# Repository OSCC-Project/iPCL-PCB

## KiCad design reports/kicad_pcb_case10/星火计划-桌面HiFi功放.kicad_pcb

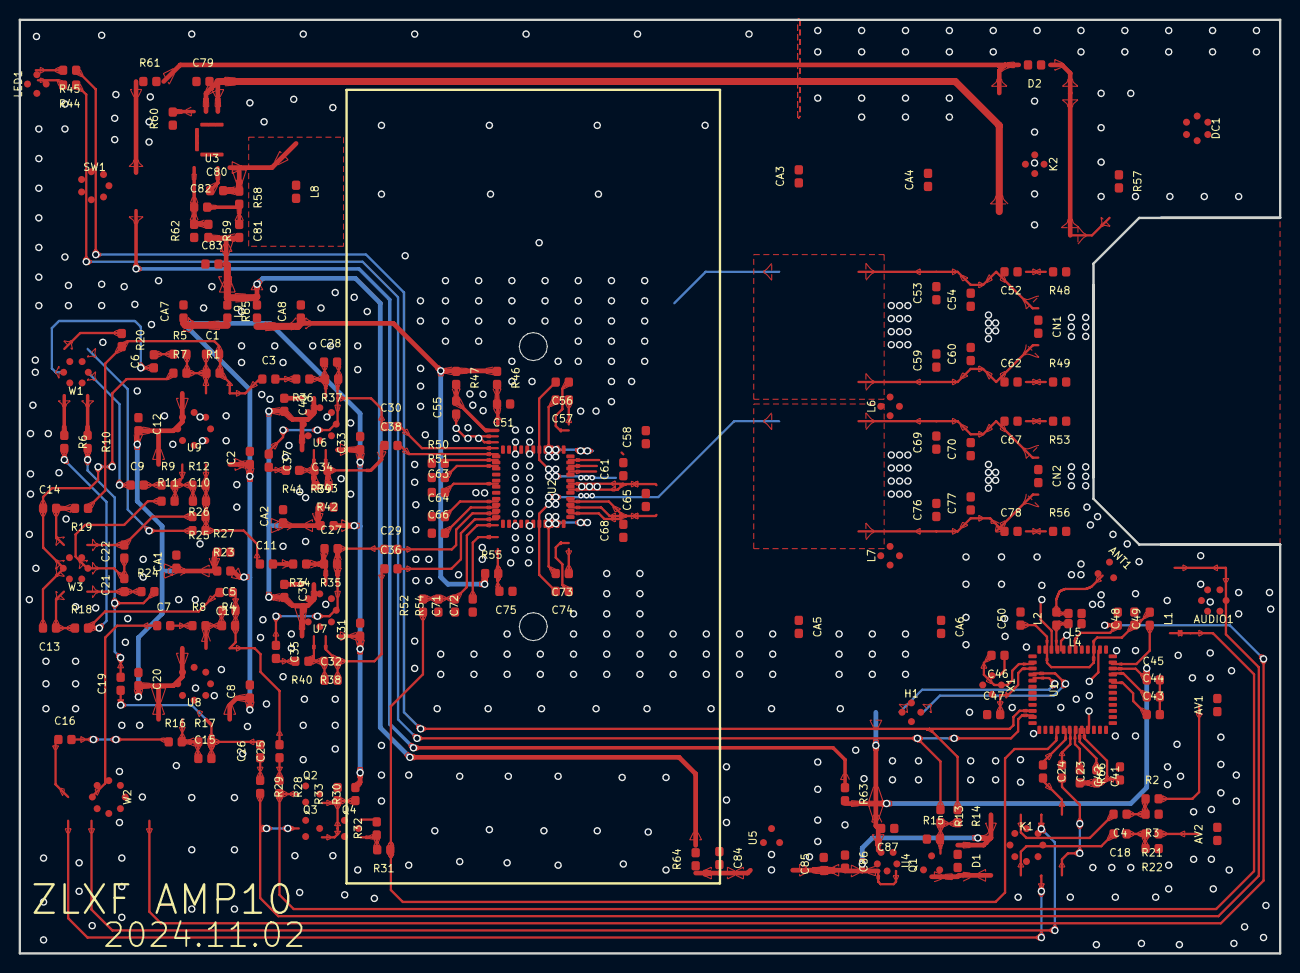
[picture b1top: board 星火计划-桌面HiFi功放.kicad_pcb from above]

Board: 4 copper layers, 135.0 x 100.0 mm, 200 parts (0 on the bottom side), 129 nets.

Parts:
ANT1: e326
AUDIO1: e334
AV1: e336
AV2: e338
C1, C8, C47, C55, C73, C80, C82: b67ced7d9c4142d5889f59f851f02ee1
C2: e212
C3, C16, C86: 7f84295a007640f69b0a8ec1af986fde
C4: e178
C5: e156
C6: e224
C7: e532
C9: e228
C10: e218
C11: e522
C12: e214
C13: e232
C14: e234
C15: e166
C17: e528
C18: e180
C19: e530
C20: e160
C21: e236
C22: e238
C23: e516
C24: e518
C25: e512
C26: e514
C27: e284
C28: e268
C29: e380
C30: e384
C31: e280
C32: e290
C33: e264
C34: e274
C35: e520
C36: e378
C37: e526
C38: e382
C39: e276
C40: e260
C41: e21
C42: e1
C43: e24
C44: e26
C45: e28
C46: e36
C48: e30
C49: e322
C50: e32
C51: e406
C52: e452
C53: e436
C54: e444
C56: e416
C57: e418
C58: e422
C59: e438
C60: e446
C61: e426
C62: e454
C63: e386
C64: e388
C65, C79: 1365614aeabe428f99748ceac79feb32
C66: e390
C67: e460
C68: e420
C69: e440
C70: e448
C71: e398
C72: e376
C74: e410
C75: e374
C76: e442
C77: e450
C78: e462
C81: e352
C83: e360
C84: e488
C85: e490
C87: e496
CA1: e202
CA2: e258
CA3: e428
CA4: e432
CA5: e430
CA6: e434
CA7: e364
CA8: e368
CN1: e468
CN2: e470
D1: e502
D2: e492
DC1: e472
H1: b437e88b1ebd4443bac505645929075e
K1: e168
K2: e476
L1: e310
L2: e294
L4: e296
L5: e298
L6, L7: 8697b58b9ffd476a9ef13f1fa45ef42a
L8: e348
L9: e366
LED1: e330
Q1: e504
Q2: e188
Q3: e190
Q4: e186
R1: e208
R2: e170
R3: e172
R4: e154
R5: e220
R6: e246
R7: e222
R8: e158
R9: e226
R10: e244
R11: e230
R12: e216
R13: e508
R14: e510
R15: e506
R16: e162
R17, R62: 512f0535ef3e460e8e596d6ccb07729c
R18: e206
R19: e240
R20: e248
R21: e174
R22: e176
R23: e0
R24: e204
R25: e242
R26: e250
R27: e18
R28: e182
R29: e184
R30: e252
R31: e196
R32: e194
R33: e192
R34: e282
R35: e278
R36: e266
R37: e262
R38: e288
R39: e272
R40: e286
R41: e270
R42: e20
R43: e22
R44: e324
R45: e332
R46: e370
R47: e402
R48: e456
R49: e458
R50: e392
R51: e394
R52: e400
R53: e464
R54: e396
R55: e372
R56: e466
R57: e474
R58: e350
R59: e356
R60: e344
R61: e478
R63: e482
R64: e486
R65: e362
R66: e1645
SW1: e480
U1: 53b0842d4baf462396c1d88187a7af27
U2: e37
U3: 8710f344c89743469ec2d2cc8cdb45c2
U4: e494
U5: e484
U6: e536
U7: e540
U8: e542
U9: e544
W1: e146
W2: e150
W3: e148
X1: e316

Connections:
$1N52139: C28.1, R36.1, R37.2, U6.2
$1N52142: C34.1, R39.2, R41.1, U6.6
$1N52143: C34.2, C38.1, R39.1, U6.7
$1N52150: C32.1, R38.2, R40.1, U7.6
$1N52151: C32.2, C36.1, R38.1, U7.7
$1N52160: C28.2, C30.1, C37.1, R37.1, U6.1
$1N52161: C27.2, C29.1, C35.1, R35.1, U7.1
$1N52162: C27.1, R34.1, R35.2, U7.2
$1N52165: C35.2, R40.2
$1N52167: C37.2, R41.2
$1N52173: C5.1, R4.1, R8.2, U8.2
$1N52174: C7.2, R8.1
$1N52175: C16.2, R16.1
$1N52176: C15.1, R16.2, R17.1, U8.6
$1N52187: C7.1, W2.5
$1N52188: C16.1, W2.2
$1N52189: K1.6, W2.6
$1N52193: C4.2, K1.7
$1N52194: C18.2, K1.2
$1N52195: C24.2, K1.5
$1N52196: C23.2, K1.4
$1N52200: C25.1, R28.1
$1N52201: C26.1, R29.1
$1N52202: C5.2, C17.1, C25.2, R4.2, U8.1
$1N52213: C15.2, C19.1, C26.2, R17.2, U8.7
$1N52222: Q4.1, R31.2, R32.1
$1N52239: R10.1, W1.1
$1N52240: R6.1, W1.4
$1N52241: C6.1, W1.5
$1N52242: C9.1, W1.2
$1N52243: C6.2, R5.1
$1N52244: C9.2, R9.1
$1N52245: C13.1, R18.1, W3.4
$1N52246: C14.2, R19.2, W3.6
$1N52247: C21.1, R24.1, W3.1
$1N52248: C22.2, R25.2, W3.3
$1N52249: C10.1, R9.2, R11.2, R12.1, U9.6
$1N52250: C21.2, C22.1, R11.1, W3.2
$1N52253: C4.1, R2.1, R3.2
$1N52256: AUDIO1.4, AUDIO1.5, Q2.3, R28.2
$1N52257: AUDIO1.3, AUDIO1.6, Q3.3, R29.2
$1N52259: D1.2, K1.1, Q1.3
$1N52261: Q1.1, R13.2, R14.2, R15.2
$1N52268: C18.1, R21.2, R22.2
$1N52271: AV2.2, R21.1
$1N52277: AV1.2, R2.2
$1N52281: Q2.1, Q3.1, Q4.3, R30.1, R33.1
$1N52290: K1.3, W2.3
$1N52296: C17.2, R6.2, R18.2
$1N52301: C19.2, R10.2, R24.2
$1N52306: R26.1, W1.3
$1N52310: C10.2, C11.1, R12.2, R25.1, R26.2, U9.7
$1N52323: R20.1, W1.6
$1N52327: C1.2, C3.1, R1.2, R19.1, R20.2, U9.1
$1N52340: C1.1, R1.1, R5.2, R7.2, U9.2
$1N52353: C13.2, C14.1, R7.1, W3.5
$1N52359: C11.2, R34.2
$1N52365: C3.2, R36.2
$1N52506: C39.2, C40.2, CA2.1, R42.1, R43.1, U6.3, U6.5, U7.3, U7.5
$2N1014: C41.1, U1.44
$2N1015: C42.1, U1.43
$2N1023: C47.2, U1.26, X1.3
$2N1029: L1.2, U1.12
$2N1042: C46.2, U1.25, X1.1
$2N1051: LED1.1, R44.2
$2N1052: LED1.3, R45.2
$2N2752: ANT1.1, L2.2, L5.2
$3N1800: C72.2, U2.20
$3N1801: C63.2, U2.11
$3N1802: C64.2, U2.14
$3N1803: C66.2, U2.15
$3N1804: R50.2, U2.7
$3N1806: R51.2, U2.8
$3N1808: C71.2, R52.2, R54.2, U2.18
$3N1809: C51.2, R46.2, U2.1
$3N1810: C75.2, R55.2, U2.22
$3N1812: C55.2, R47.2, U2.2
$3N1814: C74.1, U2.24
$3N1815: C73.1, U2.23
$3N1816: C73.2, L7.1, U2.27, U2.28
$3N1817: C74.2, L7.4, U2.32
$3N1818: C57.1, U2.44
$3N1819: C56.1, U2.43
$3N1820: C56.2, L6.1, U2.35
$3N1821: C57.2, L6.4, U2.39, U2.40
$3N1825: C52.1, R48.2
$3N1826: C62.2, R49.1
$3N1828: C67.1, R53.2
$3N1829: C78.2, R56.1
$3N1831: C52.2, C53.2, C54.2, CN1.2, L6.3
$3N1832: C59.1, C60.1, C62.1, CN1.1, L6.2
$3N1833: C67.2, C69.2, C70.2, CN2.2, L7.3
$3N1834: C76.1, C77.1, C78.1, CN2.1, L7.2
$4N1363: DC1.1, R57.1
$4N1366: R61.1, SW1.2
$4N1368: R63.1, SW1.5
$4N1371: D2.2, K2.1, R61.2
$4N1372: D2.1, K2.3, K2.4, R57.2
$4N2025: R60.2, U3.4
$4N2031: C80.1, U3.7
$4N2032: C80.2, L8.1, R58.1, U3.8
$4N2033: C81.1, C82.2, R58.2
$4N2034: C82.1, R59.1, R62.2, U3.5
$4N2458: C84.2, R64.1, U5.1
+3V7: C45.1, C87.2, H1.1, R63.2, U1.11, U4.5
+5V: C85.1, C86.2, D1.1, K1.8, U4.1, U4.3, U5.3
+6V_A: C12.2, C20.2, CA1.1, R23.1, R27.1, U8.3, U8.5, U9.3, U9.5
+12V: C81.2, C83.2, L8.2, L9.2, R59.2, R64.2, R65.1
+12V_OPA: C2.1, C8.1, C31.1, C33.1, CA7.1, R23.2, R30.2, R42.2, R65.2, U6.8, U7.8, U8.8, U9.8
+12V_PA: CA8.1, L9.1, R46.1, R47.1, R55.1
AGND: C41.2, C42.2, R66.1, U1.45
BT_ANT: L2.1, L4.2, U1.22
DACL: C23.1, U1.42
DACR: C24.1, U1.41
GND: ANT1.2, AUDIO1.1, AUDIO1.2, AV1.1, AV2.1, C2.2, C8.2, C12.1, C20.1, C31.2, C33.2, C39.1, C40.1, C43.2, C44.2, C45.2, C46.1, C47.1, C48.2, C49.1, C50.2, C51.1, C53.1, C54.1, C55.1, C58.2, C59.2, C60.2, C61.1, C63.1, C64.1, C65.2, C66.1, C68.1, C69.1, C70.1, C71.1, C72.1, C75.1, C76.2, C77.2, C79.1, C83.1, C84.1, C85.2, C86.1, C87.1, CA1.2, CA2.2, CA3.2, CA4.2, CA5.2, CA6.2, CA7.2, CA8.2, DC1.2, DC1.3, H1.4, L4.1, L5.1, LED1.2, LED1.4, Q1.2, Q2.2, Q3.2, Q4.2, R3.1, R15.1, R22.1, R27.2, R32.2, R33.2, R43.2, R48.1, R49.2, R50.1, R51.1, R53.1, R54.1, R56.2, R60.1, R62.1, R66.2, SW1.1, SW1.6, SW1.7, U1.13, U1.21, U1.23, U1.46, U2.3, U2.4, U2.12, U2.13, U2.25, U2.26, U2.33, U2.34, U2.41, U2.42, U3.1, U3.9, U4.2, U5.2, U6.4, U7.4, U8.4, U9.4, W2.1, W2.4, W2.7, X1.2, X1.4
INPUT_A: C30.2, U2.5
INPUT_B: C38.2, U2.6
INPUT_C: C29.2, U2.16
INPUT_D: C36.2, U2.17
LEDB: R14.1, R45.1, U1.35
LEDR: R13.1, R44.1, U1.36
MUTE: R31.1, R52.1, U1.39
PVDD: C58.1, C61.2, C65.1, C68.2, C79.2, CA3.1, CA4.1, CA5.1, CA6.1, K2.2, U2.29, U2.30, U2.31, U2.36, U2.37, U2.38, U3.2, U3.3
PWRKEY: C49.2, U1.18, W2.8
USBDM: H1.3, U1.27
USBDP: H1.2, U1.28
VDDBT: C48.1, C50.1, L1.1, U1.14, U1.24
VDDCORE: C43.1, U1.8
VDDIO: C44.1, U1.10

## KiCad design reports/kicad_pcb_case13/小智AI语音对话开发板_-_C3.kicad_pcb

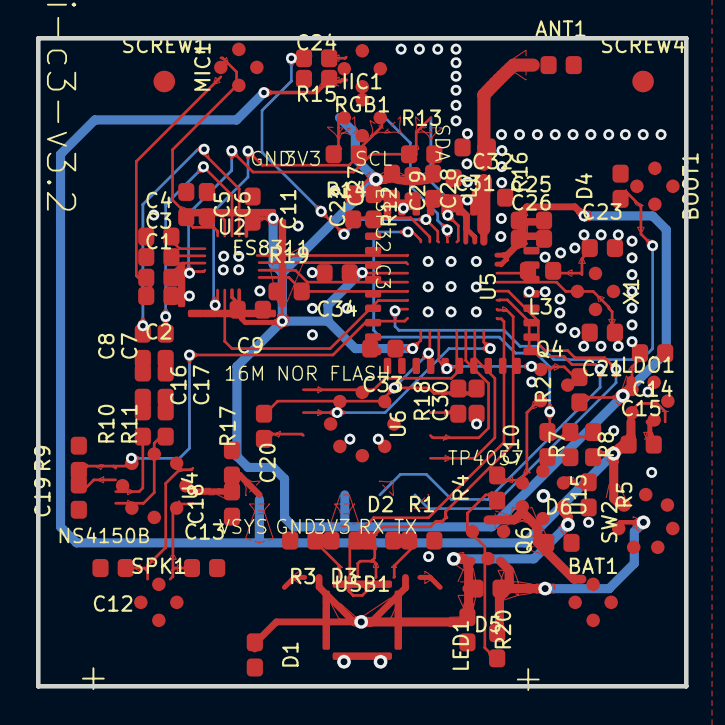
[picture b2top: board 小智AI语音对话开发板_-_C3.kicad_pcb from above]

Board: 4 copper layers, 36.0 x 36.0 mm, 82 parts (0 on the bottom side), 57 nets.

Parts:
ANT1: 114122dcd07c475ebe40200aac76a093
BAT1: 836278af07de4edf9717d25b6ec65016
BOOT1: b3649e5cefb54f17903855245019f32a
C1, C2, C3, C4, C5, C6, C7, C8, C9, C10, C11, C12, C13, C14, C15, C16, C17, C18, C19, C22, C24, C25, C26, C28, C29, C30, C31, C32, C33, C34: 0ec62e40828d4649aa19c65134dcb0f5
C20, C21, C23, C27: 05a7991f1fa1490d8ece4ac6b500d086
D1, D2, D3, D4: 5da73ff9f551480da16234f862db01d0
D5, D6: 4bc27e2758634bc9917c132c31711e3e
IIC1: 3eaa967f507248c1ac516cae81986540
L1: 03394a9e29844b04822005f3f100cdb5
L3: 74fb0f8e922542549bbf8588ec507ccb
LDO1: 5fba15a48d254445a61ad9a6e52f1692
LED1: 3863a6ce95bc411989e1282ae348fc22
MIC1: 8ee6189173c347bc8e70b77e870f6d5d
Q4: d42a5814d8404c1480ba23637be35821
Q6: 98a6dc606e334f6aaebd60298df2d4b0
R1, R3, R4, R5, R7, R8, R9, R10, R11, R12, R13, R14, R15, R16, R17, R18, R19, R20: 625c84422b324783a92dfa608e7f2de8
R2: 2e941da7b38949f292290ccf550d47f4
RGB1: d0f5c3af5dc54069b8cec1629f10b6eb
SCREW1, SCREW4: 8218aa3217414522bb9d0675a3a9d820
SPK1: 836278af07de4edf9717d25b6ec65016
SW2: ef9e1cfde34a434b98abd3df30ee1c51
U2: b9ed25adae7247a4a615f87e0d6ab6b0
U4: db83f0b44aab47c98d8228258cb0e0b4
U5: 94ebbbc58b5d4ce1b5e713e5698fcb59
U6: d56c3286f2a54943b777986e50464eac
U15: f8ff3a072edc41319181636897a8a1f5
USB1: 16bae89f927a4bc4a42fc9950053189a
X1: 1ae716d6e94945b49937000d937cc2f3

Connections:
$1N12989: R1.1, USB1.10
$1N12990: R3.1, USB1.4
$1N13022: C29.1, L1.2, U5.2, U5.3
$1N13025: C32.1, R16.2, U5.1
$1N13026: C21.1, U5.29, X1.3
$1N13046: R17.1, U6.3
$1N13050: R18.1, U6.7
$1N13079: C8.2, U2.12
$1N13080: C7.2, U2.13
$1N13089: C6.2, U2.14
$1N13091: C4.2, U2.16
$1N13092: C3.2, U2.17
$1N13093: C1.2, U2.18
$1N13096: R10.1, U4.3
$1N13097: R11.1, U4.4
$1N13099: C19.2, U4.2
$1N13104: C16.2, R10.2
$1N13105: C17.2, R11.2
$1N13116: ANT1.1, C31.1, R16.1
$1N13159: C1.1, C2.2, MIC1.1
$1N13162: C13.1, SPK1.2, U4.5
$1N13163: C12.1, SPK1.1, U4.8
$1N13174: L3.2, U5.30
$1N13175: C23.1, L3.1, X1.1
$1N14077: R5.1, U15.6
$1N14091: LED1.1, R4.1
$1N14095: Q4.1, R4.2, U15.1
$1N14634: R15.1, RGB1.4
CHIP_EN: C22.1, R12.2, U5.7
ESP_BAT_ADC: C10.2, R7.2, R8.1, U5.8
ESP_BAT_CHRG: Q4.3, R2.2, U5.19
ESP_BOOT: BOOT1.4, D4.1, U5.15
ESP_RGBLED: R15.2, U5.6
ESP_SPICLK: U5.22, U6.6
ESP_SPICS0: U5.21, U6.1
ESP_SPID: U5.23, U6.5
ESP_SPIQ: U5.24, U6.2
ESP_VDD_SPI: C30.2, R17.2, R18.2, U5.18, U6.8
GND: BAT1.2, BAT1.3, BAT1.4, BOOT1.1, BOOT1.2, BOOT1.3, C2.1, C3.1, C4.1, C5.1, C6.1, C9.1, C10.1, C11.1, C12.2, C13.2, C14.1, C15.2, C18.1, C19.1, C20.1, C21.2, C22.2, C23.2, C24.1, C25.2, C26.2, C27.1, C28.2, C29.2, C30.1, C31.2, C32.2, C33.2, C34.2, D1.2, D2.2, D3.2, D4.2, D6.2, IIC1.1, LDO1.2, MIC1.2, MIC1.3, Q4.2, R1.2, R3.2, R5.2, R8.2, R9.2, R20.2, RGB1.3, SPK1.3, SPK1.4, SW2.4, SW2.5, U2.5, U2.10, U2.20, U2.21, U4.7, U5.33, U5.e114, U5.e115, U5.e116, U5.e117, U6.4, U15.2, USB1.1, USB1.12, USB1.13, USB1.14, X1.2, X1.4
I2S_BCK: R19.2, U2.6, U5.13
I2S_DI: U2.7, U5.12
I2S_DO: U2.9, U5.9
I2S_MCK: U2.2, U5.14
I2S_WS: U2.8, U5.10
PA_EN: R9.1, U4.1, U5.16
PA_IN+: C8.1, C16.1
PA_IN-: C7.1, C17.1
SYS_I2C_SCL: IIC1.3, R14.1, U2.1, U5.5
SYS_I2C_SDA: IIC1.4, R13.1, U2.19, U5.4
USB_DN: D3.1, U5.25, USB1.5, USB1.7
USB_DP: D2.1, U5.26, USB1.6, USB1.8
USB_VBUS: D1.1, D5.2, Q6.1, R20.1, U15.4, USB1.2, USB1.11
VBAT: BAT1.1, D6.1, Q6.3, U15.3
VDD_3V3: C9.2, C11.2, C14.2, C25.1, C26.1, C27.2, C28.1, C33.1, C34.1, IIC1.2, L1.1, LDO1.5, R2.1, R12.1, R13.2, R14.2, R19.1, U2.3, U2.4, U2.11, U5.11, U5.17, U5.31, U5.32
VMIC: C5.2, MIC1.4, U2.15
VOUT: D5.1, LED1.2, Q6.2, SW2.2
VSYS: C15.1, C18.2, C20.2, C24.2, LDO1.1, LDO1.3, R7.1, RGB1.1, SW2.3, U4.6

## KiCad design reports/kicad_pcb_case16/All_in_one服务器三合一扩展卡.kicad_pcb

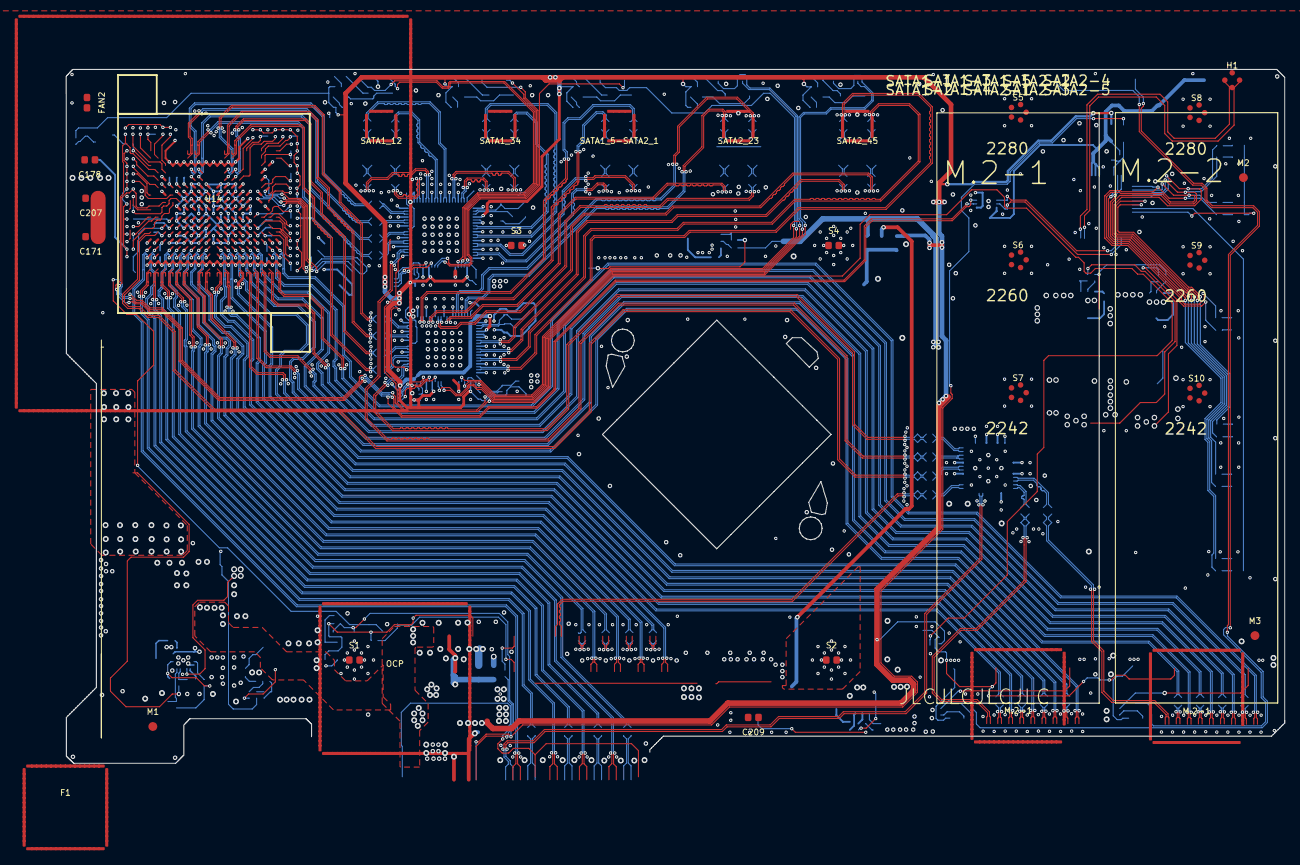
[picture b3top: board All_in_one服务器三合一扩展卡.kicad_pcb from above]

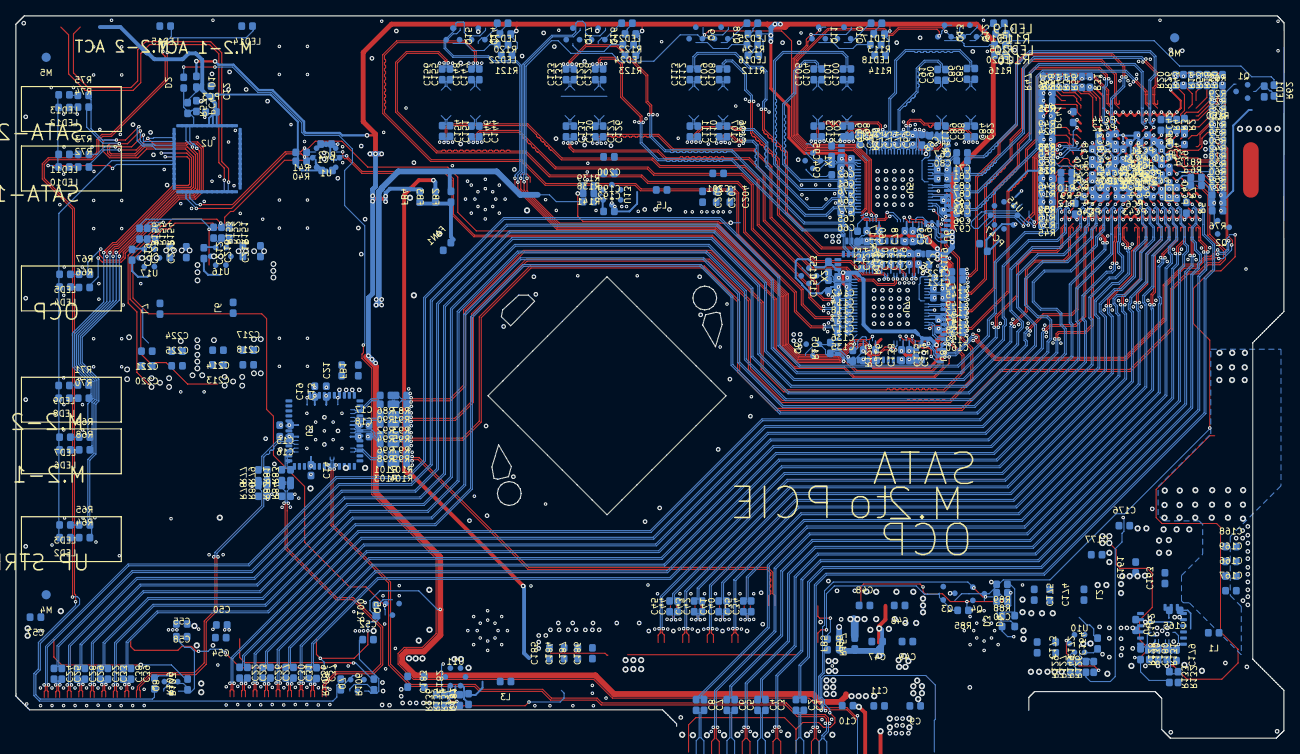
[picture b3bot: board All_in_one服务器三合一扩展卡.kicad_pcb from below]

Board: 4 copper layers, 165.1 x 94.0 mm, 506 parts (477 on the bottom side), 428 nets.

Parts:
C1, C2, C3, C4, C5, C6, C7, C8, C13, C14, C15, C16, C17, C18, C19, C20, C22, C23, C24, C25, C26, C27, C28, C29, C30, C31, C32, C33, C34, C35, C36, C37, C38, C39, C40, C41, C42, C43, C44, C45, C50, C58, C59, C60, C61, C62, C63, C64, C65, C66, C67, C68, C69, C70, C71, C72, C73, C74, C75, C76, C77, C78, C79, C80, C81, C82, C83, C84, C85, C86, C87, C88, C89, C90, C91, C92, C93, C94, C95, C96, C97, C98, C99, C100, C101, C102, C103, C104, C105, C106, C107, C108, C109, C110, C111, C112, C113, C114, C115, C116, C117, C118, C119, C120, C121, C122, C123, C124, C125, C126, C127, C128, C129, C130, C131, C132, C133, C134, C135, C136, C137, C138, C139, C140, C141, C142, C143, C144, C145, C146, C147, C148, C149, C150, C151, C152, C153, C154, C155, C156, C157, C158, C159, C160, C164, C180, C181, C192, C212, C219: e64582d333ab4f7eaead7464c60f4cf7
C9, C46, C162, C163, C172, C173, C182, C183, C199, C200, C215, C216, C222, C223: df7c6bd1564449659b13c8cb4b2059ac
C10, C11, C12, C21, C47, C48, C49, C52, C54, C55, C57, C166, C167, C168, C169, C174, C175, C176, C177, C184, C185, C186, C187, C201, C202, C203, C204, C213, C214, C217, C218, C220, C221, C224, C225: 9169ac214b8945ffa1745023983d31db
C161: 82de486334f2423a9f8b0a20a3e3185c
C165: ff8013697f5b429ea424b5998c59847b
C171, C178, C207, C209: 84c4c3c66cf0495cafe93f368514a770
C179: 3891cc3eac5e4b9f999c54e8303817f2
D1, D2, D3, D4: 07a96ceff79a4477a3dcc58816ce39df
F1: e10049
FAN1: 18143fb028a24c76acee63a367fa08d7
FAN2: dfbdf6ec425f484e89015e619c33347a
FB1, FB2, FB3, FB4, FB5, FB6: 5e9218857ab1425ca80d55ca7157db4f
H1: 32b8d1de735b4e1cbe57505ba528c018
L1: 6f8981c997a74772a245f87700a9c39a
L2, L5, L6, L7: c0729390f72e43fe838b318c95aebe10
L3: 96705fca39cf4fec8052c87db499cabf
LED1, LED2, LED4, LED6, LED8, LED10, LED12: 2498656ebd6a4133a42301cf8a2ad9b4
LED3, LED5, LED7, LED9, LED11, LED13: 04027aec9b324777bc7d483de912cb81
LED14, LED15, LED16, LED17, LED18, LED19, LED20, LED21, LED22, LED23, LED24, LED25: f7cefba8905c48ccb5158f4208dfe725
M1: e99
M2: e113
M3: e114
M4, M5, M6: a5a023e55fbb4e9aa8d432901ad8cb72
M.2-1, M.2-1#2: 2b4f392cd76d411ea4ec39c255018edc
OCP: a05605a513c84e16976cefef24cc5d2f
PC1, PC2, PC3, PC4, PC47: e64582d333ab4f7eaead7464c60f4cf7
PC5, PC6, PC7, PC8, PC9, PC10, PC11, PC12, PC13, PC14, PC15, PC16, PC17, PC18, PC19, PC20, PC21, PC22, PC23, PC24, PC25, PC26, PC27, PC28, PC29, PC30, PC31, PC32, PC33, PC34, PC35, PC36, PC37, PC38, PC39, PC40, PC41, PC42, PC43, PC44, PC45, PC46: 56d8ee5e8a5e4acc88448c0da59250ff
Q1, Q2, Q3, Q4, Q5, Q6, Q9, Q10, Q11, Q12, Q13, Q14, Q15, Q16, Q17, Q18: dc5d4dfbd5e249afaed3be0331ae19d7
Q7, Q8: 3b93e51395d24564b0bc5fe0e234c0e4
R1, R2, R3, R4, R5, R6, R7, R8, R9, R10, R11, R12, R13, R14, R15, R16, R17, R18, R19, R20, R21, R22, R23, R24, R25, R26, R27, R28, R29, R30, R31, R32, R33, R34, R35, R36, R37, R38, R39, R40, R41, R42, R43, R44, R45, R46, R47, R48, R49, R50, R51, R52, R53, R54, R55, R56, R57, R58, R59, R60, R61, R62, R63, R64, R65, R66, R67, R68, R69, R70, R71, R72, R73, R74, R75, R76, R78, R80, R82, R84, R85, R87, R88, R89, R91, R93, R95, R97, R99, R100, R102, R104, R105, R108, R109, R110, R111, R112, R113, R114, R115, R116, R117, R118, R119, R120, R121, R122, R123, R124, R125, R126, R127, R128, R129, R130, R131, R132, R133, R134, R135, R137, R138, R139, R141, R149, R150, R151, R153, R154, R156: 924045d5a6284a2c8ea0865d9cb2627d
R77, R79, R81, R83, R86, R90, R92, R94, R96, R98, R101, R103: 606dd56d420a401eb7515c60a8853da6
R106, R107, R136, R152, R155, R157: b84bdfb9389b49a7bf60fda5f26045eb
S1, S2, S3, S4: 48b40cafc0ed43bb93615878740e059f
S5, S6, S7, S8, S9, S10: d41c627abe8f486fac532ee0bfd2cbec
SATA1_5-SATA2_1, SATA1_12, SATA1_34, SATA2_23, SATA2_45: 018bcde256b541fab4f5b04781328944
U1: d861ff756e184d7095f0e40dd8e5896b
U2: c51d52303cfe4ca48890f7a13d0463a6
U3: 15b17b8a4423413ab8d5ddd77af9dd9b
U5, U7: 7183e3d145a346449f9fa4b3af1e9346
U6, U8: 564cbfc2cc1943baab4512943af036ef
U9: 3546be112e54452fab919f444d943ec8
U10, U11, U13, U16, U17: da249eab445a476fa0f593530c671c72
U14: 844ff7a39a3d4df593a7066c6ecd32e1
U15: d27483759e4e4c42a1ba7a2320159c18
X1, X2: a91d7b390dde4ba98de1884175d8790c

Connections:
0V9: C166.2, C167.2, C168.2, C169.2, C171.1, C207.1, L1.2, PC5.2, PC6.2, PC7.2, PC8.2, PC9.2, PC10.2, PC11.2, PC12.2, PC13.2, PC14.2, PC15.2, PC16.2, PC17.2, PC18.2, PC19.2, PC20.2, PC21.2, PC22.2, PC23.2, PC24.2, PC25.2, PC26.2, PC27.2, PC28.2, PC29.2, PC30.2, PC31.2, PC32.2, PC33.2, PC34.2, PC35.2, PC36.2, PC37.2, PC38.2, PC39.2, PC40.2, R128.2, U14.F7, U14.F8, U14.G5, U14.G7, U14.G9, U14.G11, U14.G13, U14.H6, U14.H8, U14.H10, U14.H12, U14.H14, U14.J5, U14.J7, U14.J9, U14.J11, U14.J13, U14.K6, U14.K8, U14.K10, U14.K12, U14.K14, U14.L7, U14.L9, U14.L11, U14.L13, U14.M5, U14.M6, U14.M8, U14.M9, U14.M10, U14.M14, U14.N7, U14.N8, U14.N12, U14.N13
1.25V: C62.2, C63.2, C64.2, C65.2, C66.2, C67.2, C68.2, C69.2, C70.2, C72.2, C73.2, C74.2, C75.2, C76.2, C77.2, C78.2, C79.2, C80.2, C117.2, C118.2, C119.2, C120.2, C121.2, C122.2, C123.2, C124.2, C125.2, C134.2, C135.2, C136.2, C137.2, C138.2, C139.2, C140.2, C141.2, C142.2, C201.2, C202.2, C203.2, C204.2, L5.2, R139.2, U5.5, U5.16, U5.25, U5.28, U5.32, U5.35, U5.38, U5.39, U5.42, U5.45, U5.48, U5.51, U5.54, U5.58, U5.62, U5.63, U5.66, U5.69, U5.72, U5.75, U7.5, U7.16, U7.25, U7.28, U7.32, U7.35, U7.38, U7.39, U7.42, U7.45, U7.48, U7.51, U7.54, U7.58, U7.62, U7.63, U7.66, U7.69, U7.72, U7.75
1V8: C174.2, C175.2, C176.2, C177.2, C178.1, L2.2, PC1.2, PC41.2, PC42.2, PC43.2, PC44.2, PC45.2, PC46.2, PC47.1, R16.1, R17.1, R18.1, R19.1, R20.1, R22.1, R23.1, R24.1, R25.1, R26.1, R27.1, R28.1, R30.2, R31.2, R32.2, R33.2, R34.2, R35.2, R36.2, R50.1, R51.1, R52.1, R54.1, R55.1, R56.1, R58.1, R60.1, R61.1, R76.2, R149.2, R150.2, U1.2, U9.12, U14.D16, U14.E3, U14.F13, U14.G8, U14.M7, U14.M12, U14.N9, U14.N14, U15.3, U15.7, U15.8
3.3V1: C50.1, C52.2, C54.2, C213.2, C214.2, C217.2, C218.2, L6.2, M.2-1.2, M.2-1.4, M.2-1.12, M.2-1.14, M.2-1.16, M.2-1.18, M.2-1.70, M.2-1.72, M.2-1.74, Q7.2, R152.2
3.3V2: C55.2, C57.2, C58.1, C220.2, C221.2, C224.2, C225.2, L7.2, M.2-1#2.2, M.2-1#2.4, M.2-1#2.12, M.2-1#2.14, M.2-1#2.16, M.2-1#2.18, M.2-1#2.70, M.2-1#2.72, M.2-1#2.74, Q8.2, R155.2
3V3: C11.2, C48.2, C59.2, C60.2, C61.2, C114.2, C115.2, C116.2, D1.2, D4.2, F1.A9, F1.A10, F1.B8, FB1.1, FB4.1, FB6.1, OCP.10, OCP.11, OCP.12, OCP.13, OCP.69, OCP.70, OCP.71, OCP.72, R62.2, R85.2, R88.2, R100.2, R105.2, R112.2, R113.2, R114.2, R115.2, R116.2, R117.1, R120.2, R121.2, R122.2, R123.2, R124.2, R125.1, U5.1, U5.14, U5.61, U6.7, U6.8, U7.1, U7.14, U7.61, U8.7, U8.8
3V3_AUX: C10.2, D3.2, F1.B10, FB5.1
3V3_MCU: C12.1, D1.1, H1.1, PC2.2, PC3.1, R40.1, R41.1, R57.2, U1.7, U1.8, U2.4, U2.5, U2.6
5V: C49.2, C184.2, C185.2, C186.2, C187.2, C209.1, FB3.1, L3.2, OCP.2, OCP.3, OCP.4, R135.2
12V: C9.2, C46.2, C161.1, C162.2, C163.2, C172.2, C173.2, C182.2, C183.2, C199.2, C200.2, C215.2, C216.2, C222.2, C223.2, F1.A2, F1.A3, F1.B1, F1.B2, F1.B3, FB2.1, OCP.61, OCP.62, OCP.63, R126.2, R134.2, R138.2, R153.2, R156.2, U9.2, U9.3, U9.4, U9.5, U10.3, U11.3, U13.3, U16.3, U17.3
$1N23783: R5.2, U14.N3
$1N23822: R6.2, U14.M3
$1N23861: R7.2, U14.M4
$1N23900: R8.2, U14.L4
$1N23939: R9.2, U14.M15
$1N23978: R10.2, U14.L15
$1N24017: R11.2, U14.N16
$1N24056: R12.2, U14.M16
$1N24095: R13.2, U14.L5
$1N24485: R1.1, U14.F3
$1N24524: R2.1, U14.F4
$1N24563: R3.1, U14.F5
$1N24602: R4.1, U14.F6
$2N12217: R14.2, U14.B1
$2N12227: R16.2, U14.L17
$2N12228: R17.2, U14.K17
$2N12233: R61.2, U14.A16
$2N12235: R53.2, U14.D3
$2N12237: R55.2, U14.G17
$2N12238: R56.2, U14.D13
$2N12239: R58.2, U14.E13
$2N12242: R42.2, R50.2, U14.H5
$2N12260: R51.2, U14.A18
$2N12262: R54.2, U14.L16
$2N12264: R52.2, U14.H17
$2N12266: R37.2, U14.M18
$2N12268: R38.2, U14.K1
$2N12270: R39.2, U14.J1
$2N12300: R15.1, U14.K18
$2N12304: R25.2, U14.G1
$2N12306: R24.2, U14.B18
$2N12308: R23.2, U14.F2
$2N12310: R22.2, U14.G4
$2N12312: R21.2, U14.K15
$2N12325: R28.2, U14.K4
$2N12327: R27.2, U14.H4
$2N12329: R26.2, U14.B2
$2N12331: R29.2, U14.E2
$2N12351: R20.2, U14.C3
$2N28967: LED2.2, R64.2
$2N29010: LED3.2, R65.2
$2N29127: LED5.2, R67.2
$2N29133: LED4.2, R66.2
$2N29287: LED9.2, R71.2
$2N29293: LED7.2, R69.2
$2N29299: LED8.2, R70.2
$2N29305: LED6.2, R68.2
$2N29459: LED13.2, R75.2
$2N29465: LED11.2, R73.2
$2N29471: LED12.2, R74.2
$2N29477: LED10.2, R72.2
$2N36298: LED1.2, Q1.3, R62.1
$2N54515: Q1.1, R63.1
$4N14022: Q2.1, Q3.1, Q4.3, Q5.1, Q6.1, R89.1
$4N30581: D3.1, D4.1, R89.2
$5N9110: LED14.2, R108.1
$5N9378: LED15.2, R109.1
$5N62052: Q7.1, R106.2
$5N62054: Q7.3, R108.2
$5N62098: Q8.1, R107.2
$5N62100: Q8.3, R109.2
$5N66007: OCP.77, R157.2
$6N23073: C165.2, L1.1, U9.6, U9.19, U9.20
$6N26781: C181.2, U11.6
$6N26782: C181.1, L3.1, U11.2
$6N26922: R134.1, U11.5
$6N28574: C164.2, U10.6
$6N28575: C164.1, L2.1, U10.2
$6N28576: R126.1, U10.5
$6N30193: R128.1, R131.2, U9.14
$6N48523: R139.1, R141.2, U13.4
$6N48527: C192.2, U13.6
$6N48528: C192.1, L5.1, U13.2
$6N48529: R138.1, U13.5
$6N58597: C180.2, U9.11
$6N58669: C165.1, U9.1
$6N58680: C179.2, R130.1, R133.1, U9.17
$6N58721: R130.2, U9.9
$6N67598: R132.2, R133.2, U9.15
$6N68979: R136.1, R137.2, U11.4
$6N69029: R135.1, R136.2
$6N85211: R127.2, R129.1, U10.4
$6N85261: R127.1, R149.1
$6N90884: R151.1, R152.1, U16.4
$6N90888: C212.2, U16.6
$6N90889: C212.1, L6.1, U16.2
$6N90890: R153.1, U16.5
$6N91380: R154.1, R155.1, U17.4
$6N91384: C219.2, U17.6
$6N91385: C219.1, L7.1, U17.2
$6N91386: R156.1, U17.5
$7N2161: R110.1, U5.57
$7N2164: R111.1, U5.31
$7N2169: R117.2, U5.2
$7N2212: C93.1, U5.29
$7N2215: C92.1, U5.30
$7N2216: C71.1, U5.37
$7N2217: C81.1, U5.36
$7N2222: C87.1, U5.33
$7N2224: C83.1, U5.34
$7N2548: C88.2, SATA1_12.12
$7N2549: C89.2, SATA1_12.13
$7N2550: C82.2, SATA1_12.9
$7N2551: C84.2, SATA1_12.10
$7N3417: C90.2, SATA1_12.5
$7N3418: C91.2, SATA1_12.6
$7N3419: C86.2, SATA1_12.3
$7N3420: C85.2, SATA1_12.2
$7N5688: C105.2, SATA1_34.6
$7N5689: C104.2, SATA1_34.5
$7N5690: C100.2, SATA1_34.2
$7N5691: C101.2, SATA1_34.3
$7N5694: C103.2, SATA1_34.13
$7N5695: C102.2, SATA1_34.12
$7N5696: C98.2, SATA1_34.9
$7N5697: C99.2, SATA1_34.10
$7N5996: C113.2, SATA1_5-SATA2_1.6
$7N5997: C112.2, SATA1_5-SATA2_1.5
$7N5998: C108.2, SATA1_5-SATA2_1.2
$7N5999: C109.2, SATA1_5-SATA2_1.3
$7N6002: C111.2, SATA1_5-SATA2_1.13
$7N6003: C110.2, SATA1_5-SATA2_1.12
$7N6004: C106.2, SATA1_5-SATA2_1.9
$7N6005: C107.2, SATA1_5-SATA2_1.10
$7N6304: C133.2, SATA2_23.6
$7N6305: C132.2, SATA2_23.5
$7N6306: C128.2, SATA2_23.2
$7N6307: C129.2, SATA2_23.3
$7N6310: C131.2, SATA2_23.13
$7N6311: C130.2, SATA2_23.12
$7N6312: C126.2, SATA2_23.9
$7N6313: C127.2, SATA2_23.10
$7N6612: C156.2, SATA2_45.6
$7N6613: C155.2, SATA2_45.5
$7N6614: C147.2, SATA2_45.2
$7N6615: C148.2, SATA2_45.3
$7N6618: C154.2, SATA2_45.13
$7N6619: C151.2, SATA2_45.12
$7N6620: C144.2, SATA2_45.9
$7N6621: C146.2, SATA2_45.10
$7N9147: R118.1, U7.57
$7N9150: R119.1, U7.31
$7N9155: R125.2, U7.2
$7N9199: C158.1, U7.29
$7N9202: C157.1, U7.30
$7N9203: C143.1, U7.37
$7N9204: C145.1, U7.36
$7N9209: C152.1, U7.33
$7N9211: C149.1, U7.34
$7N30033: LED17.1, Q10.3
$7N30035: LED17.2, R113.1
$7N30329: LED18.2, R114.1
$7N30331: LED18.1, Q11.3
$7N30453: LED19.2, R115.1
$7N30455: LED19.1, Q12.3
$7N30577: LED20.2, R116.1
$7N30579: LED20.1, Q13.3
$7N30701: LED16.2, R112.1
$7N30703: LED16.1, Q9.3
$7N31328: LED22.1, Q15.3
$7N31330: LED22.2, R121.1
$7N31345: LED23.1, Q16.3
$7N31347: LED23.2, R122.1
$7N31352: LED24.1, Q17.3
$7N31354: LED24.2, R123.1
$7N31359: LED25.1, Q18.3
$7N31361: LED25.2, R124.1
$7N31366: LED21.1, Q14.3
$7N31368: LED21.2, R120.1
$7N41181: C97.1, U5.26
$7N41182: C96.1, U5.27
$7N41260: C159.1, U7.27
$7N41261: C160.1, U7.26
ACT1: M.2-1.10, R106.1
ACT2: M.2-1#2.10, R107.1
B1: R65.1, U2.12
B2: R67.1, R73.1, U2.14
B3: R69.1, R75.1, U2.16
B4: R71.1, U2.18
C0+: C36.1, M.2-1.47
C0-: C37.1, M.2-1.49
C1+: C30.1, M.2-1.35
C1-: C31.1, M.2-1.37
C2+: C26.1, M.2-1.23
C2-: C27.1, M.2-1.25
C3+: C22.1, M.2-1.11
C3-: C23.1, M.2-1.13
C4+: C38.1, M.2-1#2.47
C4-: C39.1, M.2-1#2.49
C5+: C32.1, M.2-1#2.35
C5-: C33.1, M.2-1#2.37
C6+: C28.1, M.2-1#2.23
C6-: C29.1, M.2-1#2.25
C7+: C24.1, M.2-1#2.11
C7-: C25.1, M.2-1#2.13
CFG_EN: R59.2, R60.2, U14.K2
CK0+: R96.1, U3.31
CK0-: R98.1, U3.30
CK1+: R101.1, U3.26
CK1-: R103.1, U3.25
CK2+: R92.1, U3.34
CK2-: R94.1, U3.33
CK3+: R77.1, U3.9
CK3-: R79.1, U3.10
CK4+: R81.1, U3.11
CK4-: R83.1, U3.12
CK5+: R86.1, U3.36
CK5-: R90.1, U3.35
CLKVCC: C13.2, C14.2, C15.2, C16.2, C17.2, C18.2, C19.2, C21.2, FB1.2, U3.5, U3.8, U3.15, U3.29, U3.32, U3.39, U3.42, U3.45, U3.47
EE_CS: U14.G16, U15.1
EE_DI: U14.H16, U15.5
EE_DO: U14.F17, U15.2
EE_SK: U14.E16, U15.6
GD_LED#: R63.2, R150.1, U14.C1
GND: C9.1, C10.1, C11.1, C12.2, C13.1, C14.1, C15.1, C16.1, C17.1, C18.1, C19.1, C20.1, C21.1, C46.1, C47.1, C48.1, C49.1, C50.2, C52.1, C54.1, C55.1, C57.1, C58.2, C59.1, C60.1, C61.1, C62.1, C63.1, C64.1, C65.1, C66.1, C67.1, C68.1, C69.1, C70.1, C72.1, C73.1, C74.1, C75.1, C76.1, C77.1, C78.1, C79.1, C80.1, C94.2, C95.1, C114.1, C115.1, C116.1, C117.1, C118.1, C119.1, C120.1, C121.1, C122.1, C123.1, C124.1, C125.1, C134.1, C135.1, C136.1, C137.1, C138.1, C139.1, C140.1, C141.1, C142.1, C150.2, C153.1, C161.2, C162.1, C163.1, C166.1, C167.1, C168.1, C169.1, C171.2, C172.1, C173.1, C174.1, C175.1, C176.1, C177.1, C178.2, C179.1, C180.1, C182.1, C183.1, C184.1, C185.1, C186.1, C187.1, C199.1, C200.1, C201.1, C202.1, C203.1, C204.1, C207.2, C209.2, C213.1, C214.1, C215.1, C216.1, C217.1, C218.1, C220.1, C221.1, C222.1, C223.1, C224.1, C225.1, F1.A4, F1.A12, F1.A15, F1.A18, F1.A20, F1.A23, F1.A24, F1.A27, F1.A28, F1.A31, F1.B4, F1.B7, F1.B13, F1.B16, F1.B18, F1.B21, F1.B22, F1.B25, F1.B26, F1.B29, F1.B32, FAN1.2, FAN2.2, H1.4, LED1.1, LED14.1, LED15.1, M.2-1.1, M.2-1.3, M.2-1.9, M.2-1.15, M.2-1.21, M.2-1.27, M.2-1.33, M.2-1.39, M.2-1.45, M.2-1.51, M.2-1.57, M.2-1.71, M.2-1.73, M.2-1.75, M.2-1.76, M.2-1.77, M.2-1#2.1, M.2-1#2.3, M.2-1#2.9, M.2-1#2.15, M.2-1#2.21, M.2-1#2.27, M.2-1#2.33, M.2-1#2.39, M.2-1#2.45, M.2-1#2.51, M.2-1#2.57, M.2-1#2.71, M.2-1#2.73, M.2-1#2.75, M.2-1#2.76, M.2-1#2.77, OCP.1, OCP.5, OCP.6, OCP.8, OCP.9, OCP.20, OCP.21, OCP.24, OCP.25, OCP.28, OCP.29, OCP.32, OCP.33, OCP.36, OCP.37, OCP.40, OCP.41, OCP.44, OCP.45, OCP.48, OCP.49, OCP.52, OCP.53, OCP.56, OCP.57, OCP.60, OCP.64, OCP.65, OCP.67, OCP.68, OCP.73, OCP.79, OCP.82, OCP.83, OCP.86, OCP.87, OCP.90, OCP.91, OCP.94, OCP.95, OCP.98, OCP.99, OCP.102, OCP.103, OCP.106, OCP.107, OCP.110, OCP.111, OCP.114, OCP.115, OCP.118, OCP.119, OCP.120, PC1.1, PC2.1, PC3.2, PC4.2, PC5.1, PC6.1, PC7.1, PC8.1, PC9.1, PC10.1, PC11.1, PC12.1, PC13.1, PC14.1, PC15.1, PC16.1, PC17.1, PC18.1, PC19.1, PC20.1, PC21.1, PC22.1, PC23.1, PC24.1, PC25.1, PC26.1, PC27.1, PC28.1, PC29.1, PC30.1, PC31.1, PC32.1, PC33.1, PC34.1, PC35.1, PC36.1, PC37.1, PC38.1, PC39.1, PC40.1, PC41.1, PC42.1, PC43.1, PC44.1, PC45.1, PC46.1, PC47.2, Q1.2, Q2.2, Q3.2, Q4.2, Q5.2, Q6.2, Q9.2, Q10.2, Q11.2, Q12.2, Q13.2, Q14.2, Q15.2, Q16.2, Q17.2, Q18.2, R1.2, R2.2, R3.2, R4.2, R5.1, R6.1, R7.1, R8.1, R9.1, R10.1, R11.1, R12.1, R13.1, R14.1, R15.2, R21.1, R29.1, R37.1, R38.1, R39.1, R42.1, R43.1, R44.1, R45.1, R46.1, R47.1, R48.1, R49.1, R53.1, R59.1, R78.2, R80.2, R82.2, R84.2, R87.2, R91.2, R93.2, R95.2, R97.2, R99.2, R102.2, R104.2, R110.2, R111.2, R118.2, R119.2, R129.2, R131.1, R132.1, R137.1, R141.1, R151.2, R154.2, S1.1, S2.1, S3.1, S4.1, S5.1, S6.1, S7.1, S8.1, S9.1, S10.1, SATA1_5-SATA2_1.1, SATA1_5-SATA2_1.4, SATA1_5-SATA2_1.7, SATA1_5-SATA2_1.8, SATA1_5-SATA2_1.11, SATA1_5-SATA2_1.14, SATA1_5-SATA2_1.15, SATA1_5-SATA2_1.16, SATA1_12.1, SATA1_12.4, SATA1_12.7, SATA1_12.8, SATA1_12.11, SATA1_12.14, SATA1_12.15, SATA1_12.16, SATA1_34.1, SATA1_34.4, SATA1_34.7, SATA1_34.8, SATA1_34.11, SATA1_34.14, SATA1_34.15, SATA1_34.16, SATA2_23.1, SATA2_23.4, SATA2_23.7, SATA2_23.8, SATA2_23.11, SATA2_23.14, SATA2_23.15, SATA2_23.16, SATA2_45.1, SATA2_45.4, SATA2_45.7, SATA2_45.8, SATA2_45.11, SATA2_45.14, SATA2_45.15, SATA2_45.16, U1.1, U2.7, U3.13, U3.14, U3.18, U3.19, U3.22, U3.23, U3.24, U3.37, U3.43, U3.46, U3.48, U3.49, U5.77, U6.4, U6.9, U7.77, U8.4, U8.9, U9.7, U9.8, U9.10, U9.13, U9.16, U9.18, U9.21, U10.1, U11.1, U13.1, U14.A3, U14.A13, U14.B3, U14.B13, U14.C4, U14.C5, U14.C6, U14.C7, U14.C8, U14.C9, U14.C10, U14.C11, U14.C12, U14.C17, U14.F9, U14.F10, U14.F11, U14.F12, U14.G3, U14.G6, U14.G10, U14.G12, U14.G14, U14.H7, U14.H9, U14.H11, U14.H13, U14.J6, U14.J8, U14.J10, U14.J12, U14.J14, U14.J17, U14.K5, U14.K7, U14.K9, U14.K11, U14.K13, U14.L6, U14.L8, U14.L10, U14.L12, U14.L14, U14.M11, U14.M13, U14.N1, U14.N2, U14.N4, U14.N5, U14.N6, U14.N10, U14.N11, U14.N15, U14.N17, U14.N18, U14.T1, U14.T2, U14.T3, U14.T4, U14.T5, U14.T6, U14.T7, U14.T8, U14.T9, U14.T10, U14.T11, U14.T12, U14.T13, U14.T14, U14.T15, U14.T16, U14.T17, U14.T18, U15.4, U16.1, U17.1, X1.2, X1.4, X2.2, X2.4
JMB1_RX0+: C93.2, U14.E8
JMB1_RX0-: C92.2, U14.D8
JMB1_RX1+: C81.2, U14.E7
JMB1_RX1-: C71.2, U14.D7
JMB1_TX0+: C97.2, U14.B7
JMB1_TX0-: C96.2, U14.A7
JMB1_TX1+: C87.2, U14.B6
JMB1_TX1-: C83.2, U14.A6
JMB2_RX0+: C158.2, U14.E12
JMB2_RX0-: C157.2, U14.D12
JMB2_RX1+: C145.2, U14.E11
JMB2_RX1-: C143.2, U14.D11
JMB2_TX0+: C160.2, U14.B12
JMB2_TX0-: C159.2, U14.A12
JMB2_TX1+: C152.2, U14.B11
JMB2_TX1-: C149.2, U14.A11
LED0: Q13.1, U5.4
LED1: Q12.1, U5.3
LED2: Q11.1, U5.76
LED3: Q10.1, U5.12
LED4: Q9.1, U5.11
LED5: Q18.1, U7.4
LED6: Q17.1, U7.3
LED7: Q16.1, U7.76
LED8: Q15.1, U7.12
LED9: Q14.1, U7.11
M2_RST: M.2-1.50, M.2-1#2.50, Q5.3, R100.1
M2_RX0+: M.2-1.41, U14.P10
M2_RX0-: M.2-1.43, U14.R10
M2_RX1+: M.2-1.29, U14.P11
M2_RX1-: M.2-1.31, U14.R11
M2_RX2+: M.2-1.17, U14.P12
M2_RX2-: M.2-1.19, U14.R12
M2_RX3+: M.2-1.5, U14.P13
M2_RX3-: M.2-1.7, U14.R13
M2_RX4+: M.2-1#2.41, U14.P14
M2_RX4-: M.2-1#2.43, U14.R14
M2_RX5+: M.2-1#2.29, U14.P15
M2_RX5-: M.2-1#2.31, U14.R15
M2_RX6+: M.2-1#2.17, U14.P17
M2_RX6-: M.2-1#2.19, U14.R17
M2_RX7+: M.2-1#2.5, U14.P18
M2_RX7-: M.2-1#2.7, U14.R18
M2_TX0+: C36.2, U14.U10
M2_TX0-: C37.2, U14.V10
M2_TX1+: C30.2, U14.U11
M2_TX1-: C31.2, U14.V11
M2_TX2+: C26.2, U14.U13
M2_TX2-: C27.2, U14.V13
M2_TX3+: C22.2, U14.U14
M2_TX3-: C23.2, U14.V14
M2_TX4+: C38.2, U14.U15
M2_TX4-: C39.2, U14.V15
M2_TX5+: C32.2, U14.U16
M2_TX5-: C33.2, U14.V16
M2_TX6+: C28.2, U14.U17
M2_TX6-: C29.2, U14.V17
M2_TX7+: C24.2, U14.U18
M2_TX7-: C25.2, U14.V18
MCU_RST: D2.2, PC4.1, R57.1, U2.10
MCU_SCL: R40.2, U1.6, U2.25
MCU_SDA: R41.2, U1.5, U2.26
OCP0+: C34.2, OCP.88
OCP0-: C35.2, OCP.89
OCP1+: C40.2, OCP.92
OCP1-: C41.2, OCP.93
OCP2+: C42.2, OCP.96
OCP2-: C43.2, OCP.97
OCP3+: C44.2, OCP.100
OCP3-: C45.2, OCP.101
OCP_REFCLK+: OCP.85, R103.2, R104.1
OCP_REFCLK-: OCP.84, R101.2, R102.1
OCP_RST: OCP.17, Q3.3, R85.1
OCP_RX0+: OCP.30, U14.P6
OCP_RX0-: OCP.31, U14.R6
OCP_RX1+: OCP.34, U14.P7
OCP_RX1-: OCP.35, U14.R7
OCP_RX2+: OCP.38, U14.P8
OCP_RX2-: OCP.39, U14.R8
OCP_RX3+: OCP.42, U14.P9
OCP_RX3-: OCP.43, U14.R9
OCP_TX0+: C34.1, U14.U5
OCP_TX0-: C35.1, U14.V5
OCP_TX1+: C40.1, U14.U6
OCP_TX1-: C41.1, U14.V6
OCP_TX2+: C42.1, U14.U8
OCP_TX2-: C43.1, U14.V8
OCP_TX3+: C44.1, U14.U9
OCP_TX3-: C45.1, U14.V9
PERST: C20.2, D2.1, F1.A11, Q4.1, R88.1
PETX0+: C1.1, F1.A16
PETX0-: C2.1, F1.A17
PETX1+: C3.1, F1.A21
PETX1-: C4.1, F1.A22
PETX2+: C5.1, F1.A25
PETX2-: C6.1, F1.A26
PETX3+: C7.1, F1.A29
PETX3-: C8.1, F1.A30
PEX_REFCLK+: R98.2, R99.1, U14.M1
PEX_REFCLK-: R96.2, R97.1, U14.M2
PEX_RST: Q2.3, R76.1, U14.L3
PEX_SCL: R19.2, U1.3, U14.H3
PEX_SDA: R18.2, U1.4, U14.D2
PRSNT: F1.A1, F1.B17, F1.B31
R1: R64.1, U2.11
R2: R66.1, R72.1, U2.13
R3: R68.1, R74.1, U2.15
R4: R70.1, U2.17
REFCLK1+: M.2-1.55, R83.2, R84.1
REFCLK1-: M.2-1.53, R81.2, R82.1
REFCLK2+: M.2-1#2.53, R77.2, R78.1
REFCLK2-: M.2-1#2.55, R79.2, R80.1
REFCLK3+: R92.2, R93.1, U5.23
REFCLK3-: R94.2, R95.1, U5.24
REFCLK4+: R86.2, R87.1, U7.23
REFCLK4-: R90.2, R91.1, U7.24
REFCLK+: F1.A14, U3.20
REFCLK-: F1.A13, U3.21
RX0+: C89.1, U5.40
RX0-: C88.1, U5.41
RX1+: C91.1, U5.46
RX1-: C90.1, U5.47
RX2+: C103.1, U5.52
RX2-: C102.1, U5.53
RX3+: C105.1, U5.64
RX3-: C104.1, U5.65
RX4+: C111.1, U5.70
RX4-: C110.1, U5.71
RX5+: C113.1, U7.40
RX5-: C112.1, U7.41
RX6+: C131.1, U7.46
RX6-: C130.1, U7.47
RX7+: C133.1, U7.52
RX7-: C132.1, U7.53
RX8+: C154.1, U7.64
RX8-: C151.1, U7.65
RX9+: C156.1, U7.70
RX9-: C155.1, U7.71
S1: LED2.1, LED3.1, LED4.1, LED5.1, LED6.1, LED7.1, LED8.1, LED9.1, U2.19
S2: LED10.1, LED11.1, LED12.1, LED13.1, U2.20
SATA_RST: Q6.3, R105.1, U5.22, U7.22
SPI_CK1: U5.18, U6.6
SPI_CK2: U7.18, U8.6
SPI_CS1: U5.13, U6.1
SPI_CS2: U7.13, U8.1
SPI_SI1: U5.19, U6.5
SPI_SI2: U7.19, U8.5
SPI_SO1: U5.15, U6.2
SPI_SO2: U7.15, U8.2
SPI_WP1: U5.17, U6.3
SPI_WP2: U7.17, U8.3
STATION0_CFG0: R33.1, R46.2, U14.K16
STATION0_CFG1: R32.1, R45.2, U14.M17
STATION1_CFG0: R31.1, R44.2, U14.A14
STATION1_CFG1: R30.1, R43.2, U14.A1
SWCLK: H1.2, U2.36
SWDIO: H1.3, U2.35
TX0+: C82.1, U5.44
TX0-: C84.1, U5.43
TX1+: C85.1, U5.50
TX1-: C86.1, U5.49
TX2+: C98.1, U5.56
TX2-: C99.1, U5.55
TX3+: C100.1, U5.68
TX3-: C101.1, U5.67
TX4+: C106.1, U5.74
TX4-: C107.1, U5.73
TX5+: C108.1, U7.44
TX5-: C109.1, U7.43
TX6+: C126.1, U7.50
TX6-: C127.1, U7.49
TX7+: C128.1, U7.56
TX7-: C129.1, U7.55
TX8+: C144.1, U7.68
TX8-: C146.1, U7.67
TX9+: C147.1, U7.74
TX9-: C148.1, U7.73
UPE_RX0+: F1.B15, U14.R1
UPE_RX0-: F1.B14, U14.P1
UPE_RX1+: F1.B20, U14.R2
UPE_RX1-: F1.B19, U14.P2
UPE_RX2+: F1.B24, U14.R4
UPE_RX2-: F1.B23, U14.P4
UPE_RX3+: F1.B28, U14.R5
UPE_RX3-: F1.B27, U14.P5
UPE_TX0+: C2.2, U14.V1
UPE_TX0-: C1.2, U14.U1
UPE_TX1+: C4.2, U14.V2
UPE_TX1-: C3.2, U14.U2
UPE_TX2+: C6.2, U14.V3
UPE_TX2-: C5.2, U14.U3
UPE_TX3+: C8.2, U14.V4
UPE_TX3-: C7.2, U14.U4
UPSTREAM_SEL0: R36.1, R49.2, U14.C16
UPSTREAM_SEL1: R35.1, R48.2, U14.F16
UPSTREAM_SEL2: R34.1, R47.2, U14.B16
VAUX: C47.2, FB5.2, FB6.2, OCP.7, OCP.66
VFAN: FAN1.1, FAN2.1, FB2.2, FB3.2, FB4.2
WAKE: F1.B11, R157.1
XI1: C95.2, U5.59, X1.3
XI2: C153.2, U7.59, X2.3
XO1: C94.1, U5.60, X1.1
XO2: C150.1, U7.60, X2.1
